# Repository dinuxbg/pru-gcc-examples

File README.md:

# Example projects for the GNU PRU toolchain

The pru-gcc toolchain source and build instructions are located at https://github.com/dinuxbg/gnupru .

The following simple examples are available. Check the README.md in each subdirectory for detailed instructions.

## blinking-led
The "hello world" example of the embedded world. Both PRU cores of a Beaglebone Black are started to toggle GPIOs. PRU0 core is programmed in C, while the firmware for PRU1 core is written in assembler.

Two host loader examples are provided - one for the old UIO mechanism, and one for the new Remoteproc driver.

## blinking-led++
Blinking led firmware written in C++.

## button-blinking-led
Button-controlled blinking LED. Shows both basic input and basic output.

## hc-sr04-range-sensor
Remoteproc/rpmsg example for measuring distance using the HC-SR04 ultrasound range sensor.

## md5-check
Calculate MD5 checksum for a known data chunk on both the ARM loader and one PRU core. Then UIO-based loader reads and compares the two checksums.

## ov7670-cam
PRUs on a Beaglebone White fetch RGB565 streams from two OV7670 camera modules. The UIO host-side loader then saves the images from the shared DDR-SDRAM memory into PPM files. The example shows how to access shared buffers in DDR-SDRAM, and how to write time-critical code sequences in inline assembly.

## sim-hello
Simulate your PRU executable on your PC. Note that pru-run is an ISA only simulator. Digital I/O is not simulated. Neither is OCP access.

## sim-hello++
Same simulator project as sim-hello, but written in C++ instead of C.

## External Projects
Some examples are too complex to pile up in this repository, yet could be useful as a reference.
  * [BeagleMic Microphone Array](https://gitlab.com/dinuxbg/beaglemic)

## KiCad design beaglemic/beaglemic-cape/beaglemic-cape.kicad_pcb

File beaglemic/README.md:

# BeagleMic 16-channel PDM Audio Capture

# Introduction
Ever wanted to record audio from 16 PDM microphones simultanously? Now you can with a BeagleMic running on a [PocketBeagle](https://beagleboard.org/pocket) or [BeagleBone AI](https://bbb.io/ai)

Yes, you could opt for the much simpler I2S microphones. But then you won't have fun writing assembly to capture and process sixteen digital signals at more than 2MHz sample rate.

Current firmware supports:

| Feature                    | Support           |
|----------------------------|-------------------|
| PDM Bit Clock              | 2,273 MHz         |
| PCM Output Bits Per Sample | 16 bps            |
| PCM Output Sample Rate     | 35511 Samples/sec |

# Hardware
The schematic is simple. PDM microphones' digital outputs are connected directly to the PRU input pins. The PRU also drives the bit clock. I have tested on PocketBeagle and BeagleBone AI.

| PocketBeagle | BBAI  | PRU Pin | Type  | Signal               |
|----------------------|---------|-------|----------------------|
| P2.24        | P9.11 | R30_14  | Output| PDM Bit Clock        |
| P1.36        | P8.44 | R31_0   | Input | MIC0 and MIC1 Data   |
| P1.33        | P8.41 | R31_1   | Input | MIC2 and MIC3 Data   |
| P2.32        | P8.42 | R31_2   | Input | MIC4 and MIC5 Data   |
| P2.30        | P8.39 | R31_3   | Input | MIC6 and MIC7 Data   |
| P1.31        | P8.40 | R31_4   | Input | MIC8 and MIC9 Data   |
| P2.34        | P8.37 | R31_5   | Input | MIC10 and MIC11 Data |
| P2.28        | P8.38 | R31_6   | Input | MIC12 and MIC13 Data |
| P1.29        | P8.36 | R31_7   | Input | MIC14 and MIC15 Data |

Optionally, high-level software may visualize detected audio direction using a stripe of 16 LEDs hooked to two 74HC595 shift registers:

| PocketBeagle | PB GPIO | BBAI  | BBAI GPIO | Signal |
|--------------|---------|-------|-----------|--------|
|              |         | P9.30 | gpio5_12  | DS     |
|              |         | P9.28 | gpio4_17  | SHCP   |
|              |         | P9.23 | gpio7_11  | STCP   |

For each microphone pair, one microphone is configured to output data on the rising clock edge, and the other is configured to output data on the falling edge. This way we need only 8 input GPIOs to capture data from all 16 microphones.

Microphone breakout board and a PocketBeagle Cape are provided in KiCad format.

Unfortunately the breakout board is essential for a home DIY user like me, since all PDM microphones I could find are BGA. There are numerous youtube guides how to solder BGAs at home using a skillet or a toaster oven.

# Software
PRU0 takes care of driving the PDM bit clock and capturing the microphone bit data. It then runs a CIC filter to convert PDM to PCM, and feeds PCM data to PRU1.

PRU1 is retransmitting PCM data from PRU0 down to the ARM host. RPMSG is used for control commands. Shared DDRAM buffers are used for audio data.

Host audio driver presents a standard ALSA audio card, so that arecord and other standard tools can be readily used.

# Running The Example on PocketBeagle

    # Build kernel module
    sudo apt update
    sudo apt install build-essential linux-headers-`uname -r`
    cd driver
    make
    # Install kernel module
    sudo cp beaglemic.ko /lib/modules/`uname -r`/kernel/drivers/rpmsg/
    sudo depmod -a

    # Load the driver
    sudo modprobe beaglemic

    # Build PRU firmware
    cd pru
    make
    # Start the new PRU firmware
    sudo ./start.sh

    # Record audio
    arecord  -r32000  -c16 -f S16_LE -t wav out.wav
    # Hit Ctrl+C to stop.

# Running The Example on BeagleBone AI

    # Prebuilt BB AI is provided in this repo. For corresponding
    # source change, see driver/0001-Initial-BeagleMic-DTS-for-BBAI.patch
    sudo cp driver/am5729-beagleboneai-beaglemic.dtb /boot/dtbs/`uname -r`/
    sudo sed -i -e 's@#dtb=@dtb=am5729-beagleboneai-beaglemic.dtb@g' /boot/uEnv.txt
    sync
    sudo reboot

    # Build kernel module
    sudo apt update
    sudo apt install build-essential linux-headers-`uname -r`
    cd driver
    make
    # Install kernel module
    sudo cp beaglemic.ko /lib/modules/`uname -r`/kernel/drivers/rpmsg/
    sudo depmod -a

    # Load the driver
    sudo modprobe beaglemic

    # Build PRU firmware
    cd pru
    make
    # Start the new PRU firmware
    sudo ./start-bbai.sh

    # Record audio. Use second audio card, since first one is
    # the onboard HDMI.
    arecord  -D hw:1,0 -r32000  -c16 -f S16_LE -t wav out.wav
    # Hit Ctrl+C to stop.

# Folder Structure

 * beaglemic-cape - Universal cape for BeagleBone AI, PocketBeagle and iCE40HX8K-EVB. Work in progress.
 * driver - Host ALSA audio driver.
 * inmp621-breakout - INMP621 Microphone breakout. Designed to be used with beaglemic-cape. Work in progress.
 * libs - Library code. Currently contains code to drive LED ring for beaglemic-cape.
 * pocket-cape - PocketBeagle cape to be used with spm0423hd4h-breakout.
 * pru - PRU firmware.
 * spm0423hd4h-breakout - SPM0432HD4H microphone breakout. Designed to be used with pocket-cape.

# Further Work
A few ideas to improve the design:

 * If input is limited to 8 microphones, then process and output 24bit PCM data.
 * Move comb filters to PRU1, and try to add more integrators in PRU0.
 * Clean-up the cape PCB.
   * If possible, leave headers for Class-D output from spare PRUs.

# References
 * [CIC Filter Introduction](https://dspguru.com/dsp/tutorials/cic-filter-introduction/)
 * [Another CIC Filter Article](http://www.tsdconseil.fr/log/scriptscilab/cic/cic-en.pdf)
 * [Series of PDM articles and software implementations](https://curiouser.cheshireeng.com/category/projects/pdm-microphone-toys/)
 * [Another CIC Filter Article](https://www.embedded.com/design/configurable-systems/4006446/Understanding-cascaded-integrator-comb-filters)
 * [Datasheet for the PDM microphones I've used](http://media.digikey.com/PDF/Data Sheets/Knowles Acoustics PDFs/SPM0423HD4H-WB.pdf)
 * [Inspiration for high-bandwidth data acquisition](https://github.com/ZeekHuge/BeagleScope)

# Other Resources
 * https://github.com/introlab/16SoundsUSB
 * https://github.com/introlab/odas
 * https://respeaker.io/make_a_smart_speaker/

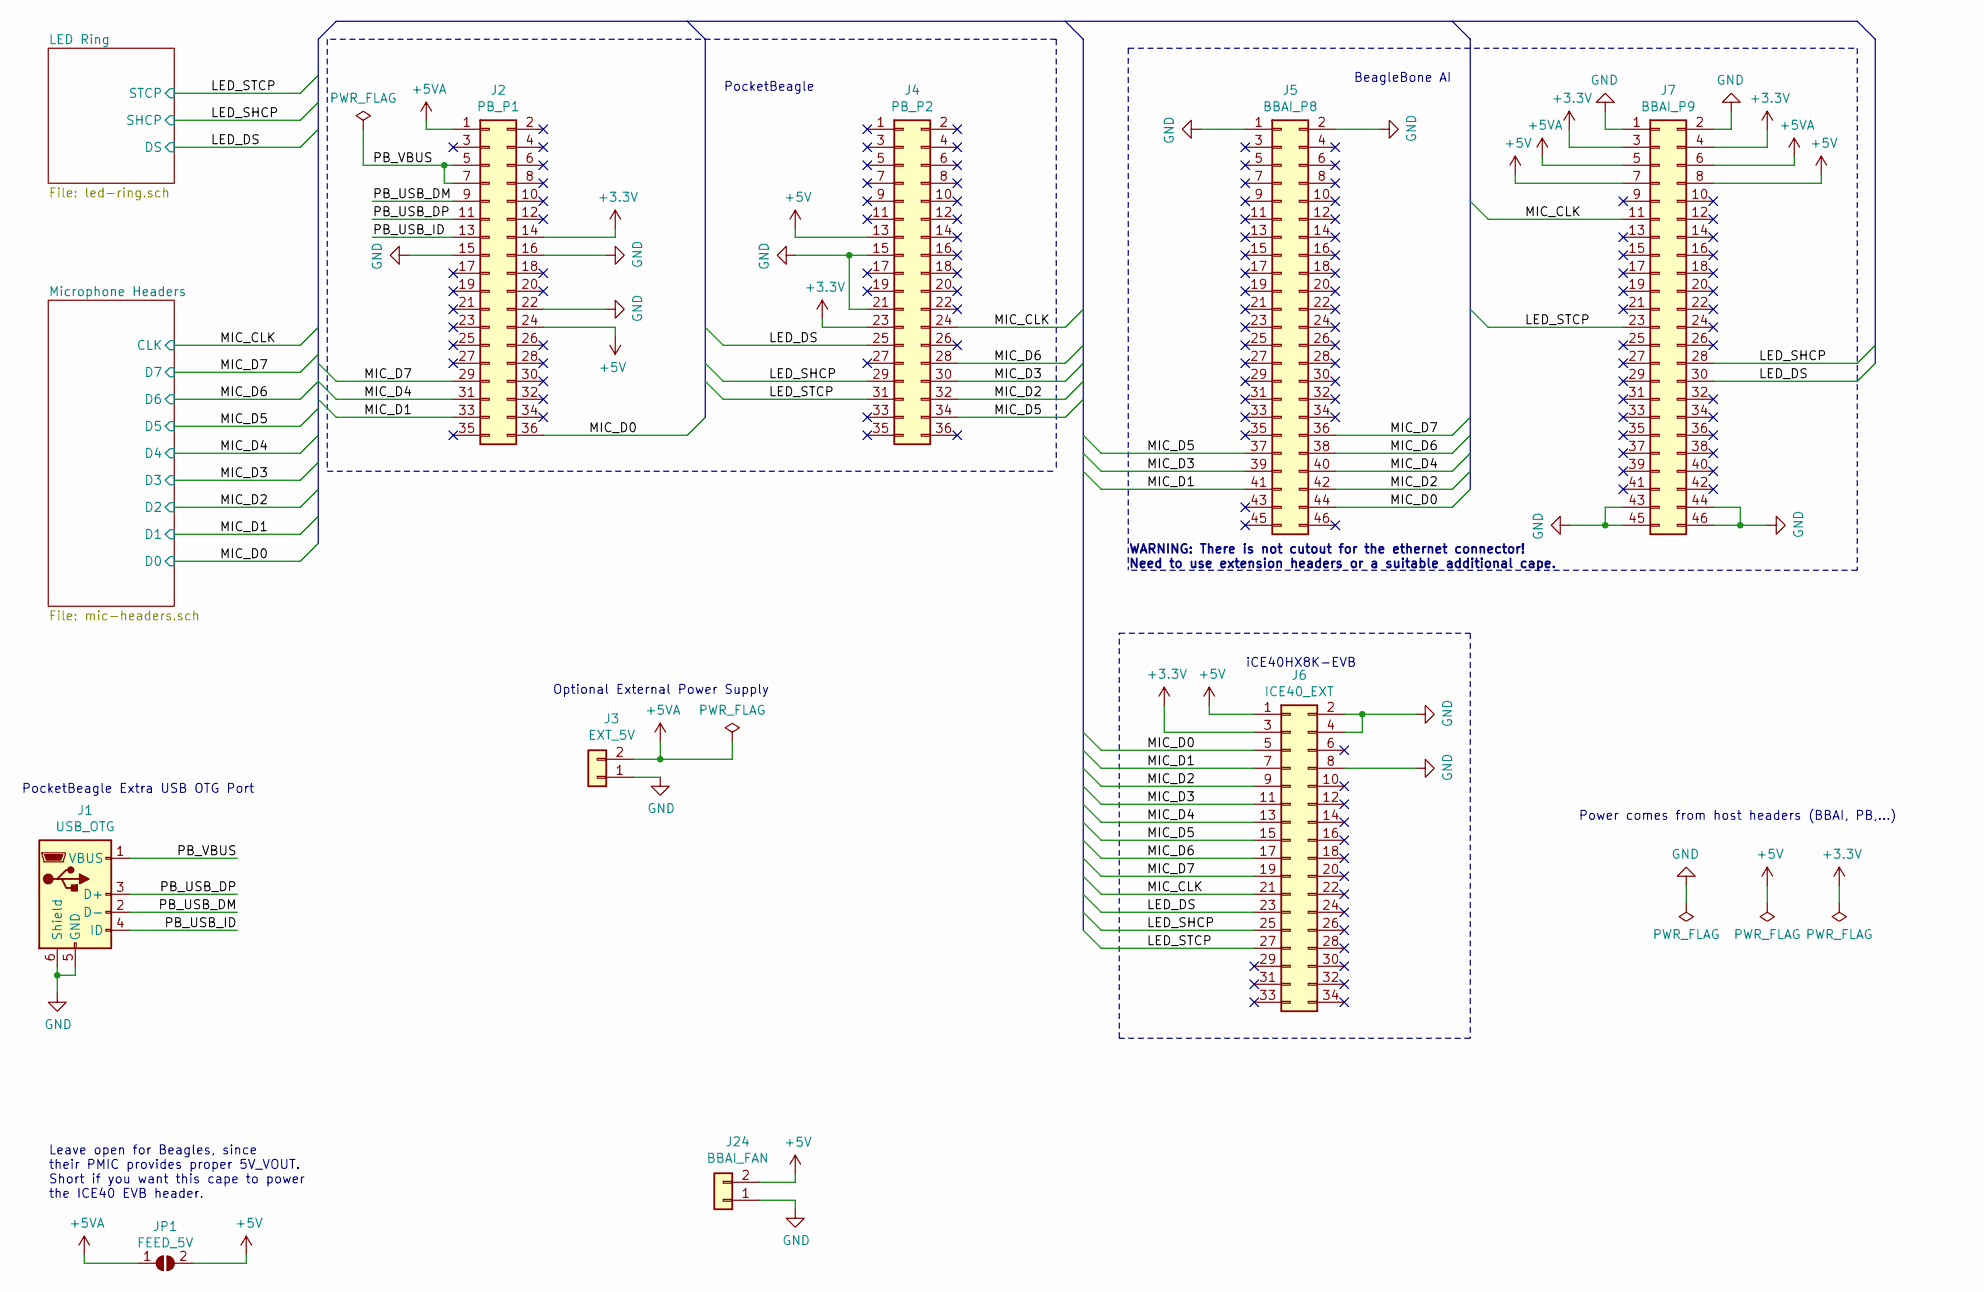
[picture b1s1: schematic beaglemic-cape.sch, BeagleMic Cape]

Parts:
J1: USB_OTG; USB_Micro-B_Tensility_54-00023_Vertical_CircularHoles
J2: PB_P1; PinHeader_2x18_P2.54mm_Vertical
J3: EXT_5V; PinHeader_1x02_P2.54mm_Vertical
J4: PB_P2; PinHeader_2x18_P2.54mm_Vertical
J5: BBAI_P8; PinSocket_2x23_P2.54mm_Vertical
J6: ICE40_EXT; PinSocket_2x17_P2.54mm_Vertical
J7: BBAI_P9; PinSocket_2x23_P2.54mm_Vertical
J24: BBAI_FAN; PinHeader_1x02_P2.54mm_Vertical
JP1: FEED_5V; SolderJumper-2_P1.3mm_Open_RoundedPad1.0x1.5mm

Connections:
+3V3: J2.14, J4.23, J6.3, J7.3, J7.4; also elsewhere on the board
+5V: J2.24, J4.13, J6.1, J7.7, J7.8, J24.2, JP1.2 (B); also elsewhere on the board
+5VA: J2.1, J3.2, J7.5, J7.6, JP1.1 (A)
/LED_DS: J4.25, J6.23, J7.30; also elsewhere on the board
/LED_SHCP: J4.29, J6.25, J7.28; also elsewhere on the board
/LED_STCP: J4.31, J6.27, J7.23; also elsewhere on the board
/MIC_CLK: J4.24, J6.21, J7.11; also elsewhere on the board
/MIC_D0: J2.36, J5.44, J6.5; also elsewhere on the board
/MIC_D1: J2.33, J5.41, J6.7; also elsewhere on the board
/MIC_D2: J4.32, J5.42, J6.9; also elsewhere on the board
/MIC_D3: J4.30, J5.39, J6.11; also elsewhere on the board
/MIC_D4: J2.31, J5.40, J6.13; also elsewhere on the board
/MIC_D5: J4.34, J5.37, J6.15; also elsewhere on the board
/MIC_D6: J4.28, J5.38, J6.17; also elsewhere on the board
/MIC_D7: J2.29, J5.36, J6.19; also elsewhere on the board
/PB_USB_DM: J1.2 (D-), J2.9
/PB_USB_DP: J1.3 (D+), J2.11
/PB_USB_ID: J1.4 (ID), J2.13
/PB_VBUS: J1.1 (VBUS), J2.5, J2.7
GND: J1.5 (GND), J1.6 (Shield), J2.15, J2.16, J2.22, J3.1, J4.15, J4.21, J5.1, J5.2, J6.2, J6.4, J6.8, J7.1, J7.2, J7.43, J7.44, J7.45, J7.46, J24.1; also elsewhere on the board

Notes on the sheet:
Power comes from host headers (BBAI, PB,...)
PocketBeagle Extra USB OTG Port
Optional External Power Supply
Leave open for Beagles, since their PMIC provides proper 5V_VOUT. Short if you want this cape to power the ICE40 EVB header.
iCE40HX8K-EVB
PocketBeagle
BeagleBone AI
WARNING: There is not cutout for the ethernet connector! Need to use extension headers or a suitable additional cape.

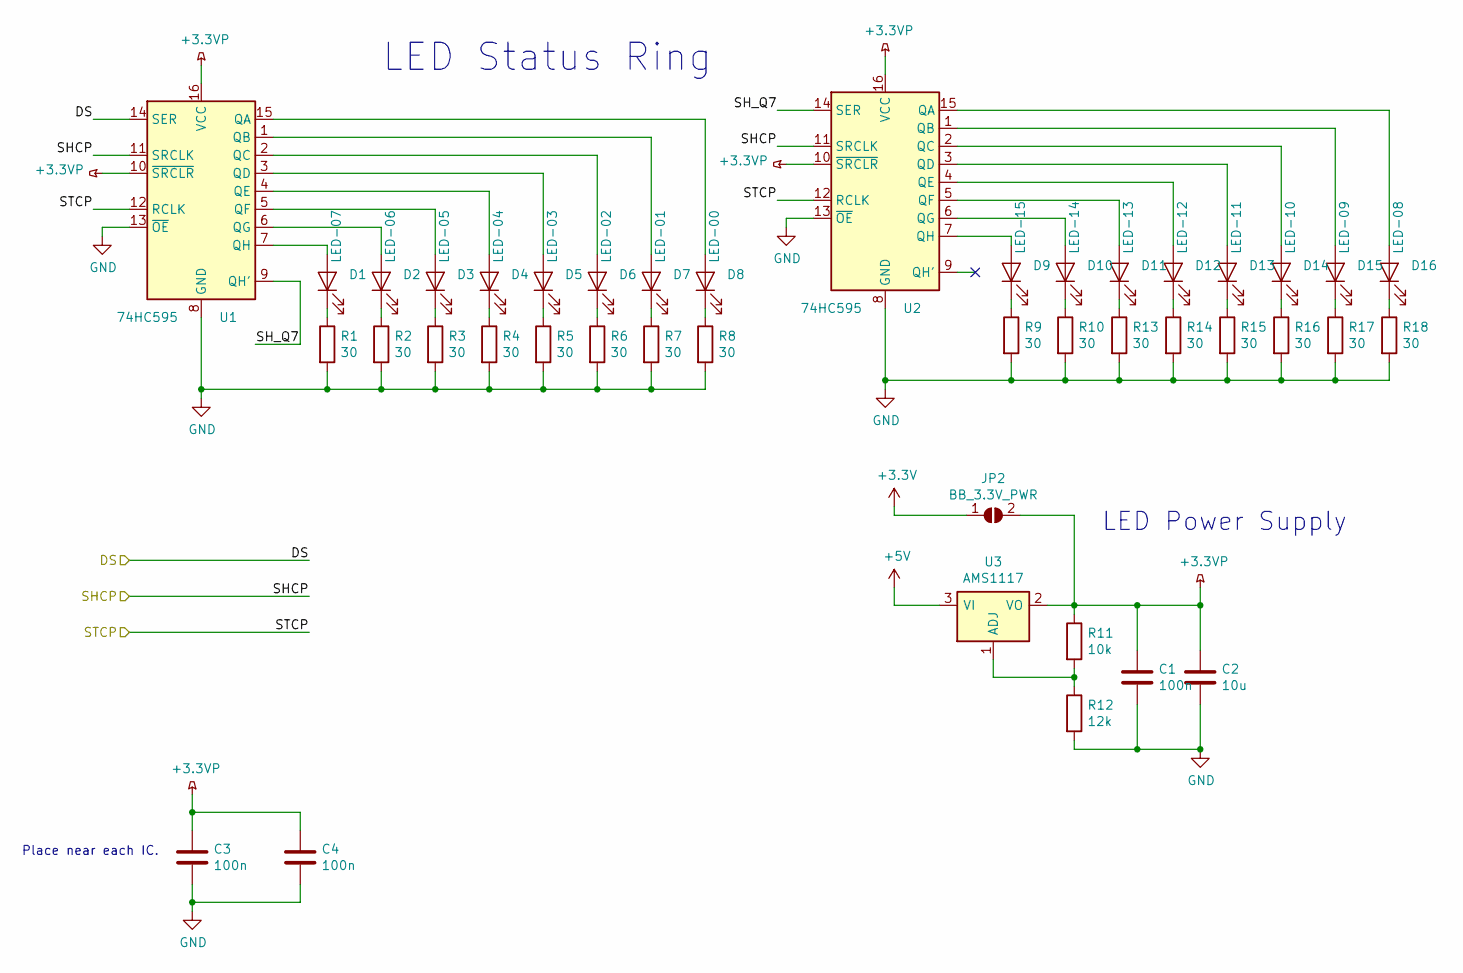
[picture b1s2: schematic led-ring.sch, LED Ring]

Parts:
C1, C3, C4: 100n; C_0805_2012Metric
C2: 10u; C_0805_2012Metric
D1: LED-07; LED_0805_2012Metric
D2: LED-06; LED_0805_2012Metric
D3: LED-05; LED_0805_2012Metric
D4: LED-04; LED_0805_2012Metric
D5: LED-03; LED_0805_2012Metric
D6: LED-02; LED_0805_2012Metric
D7: LED-01; LED_0805_2012Metric
D8: LED-00; LED_0805_2012Metric
D9: LED-15; LED_0805_2012Metric
D10: LED-14; LED_0805_2012Metric
D11: LED-13; LED_0805_2012Metric
D12: LED-12; LED_0805_2012Metric
D13: LED-11; LED_0805_2012Metric
D14: LED-10; LED_0805_2012Metric
D15: LED-09; LED_0805_2012Metric
D16: LED-08; LED_0805_2012Metric
JP2: BB_3.3V_PWR; SolderJumper-2_P1.3mm_Open_RoundedPad1.0x1.5mm
R1, R2, R3, R4, R5, R6, R7, R8, R9, R10, R13, R14, R15, R16, R17, R18: 30; R_0805_2012Metric
R11: 10k; R_0805_2012Metric
R12: 12k; R_0805_2012Metric
U1, U2: 74HC595; TSSOP-16_4.4x5mm_P0.65mm
U3: AMS1117; SOT-223-3_TabPin2

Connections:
+3.3VP: C1.1, C2.1, C3.1, C4.1, JP2.2 (B), R11.1, U1.10 (~SRCLR), U1.16 (VCC), U2.10 (~SRCLR), U2.16 (VCC), U3.2 (VO)
+3V3: JP2.1 (A); also elsewhere on the board
+5V: U3.3 (VI); also elsewhere on the board
/LED Ring/SH_Q7: U1.9 (QH'), U2.14 (SER)
/LED_DS: U1.14 (SER); also elsewhere on the board
/LED_SHCP: U1.11 (SRCLK), U2.11 (SRCLK); also elsewhere on the board
/LED_STCP: U1.12 (RCLK), U2.12 (RCLK); also elsewhere on the board
GND: C1.2, C2.2, C3.2, C4.2, R1.2, R2.2, R3.2, R4.2, R5.2, R6.2, R7.2, R8.2, R9.2, R10.2, R12.2, R13.2, R14.2, R15.2, R16.2, R17.2, R18.2, U1.8 (GND), U1.13 (~OE), U2.8 (GND), U2.13 (~OE); also elsewhere on the board
unnamed: D1.1 (K), R1.1
unnamed: D1.2 (A), U1.7 (QH)
unnamed: D2.1 (K), R2.1
unnamed: D2.2 (A), U1.6 (QG)
unnamed: D3.1 (K), R3.1
unnamed: D3.2 (A), U1.5 (QF)
unnamed: D4.1 (K), R4.1
unnamed: D4.2 (A), U1.4 (QE)
unnamed: D5.1 (K), R5.1
unnamed: D5.2 (A), U1.3 (QD)
unnamed: D6.1 (K), R6.1
unnamed: D6.2 (A), U1.2 (QC)
unnamed: D7.1 (K), R7.1
unnamed: D7.2 (A), U1.1 (QB)
unnamed: D8.1 (K), R8.1
unnamed: D8.2 (A), U1.15 (QA)
unnamed: D9.1 (K), R9.1
unnamed: D9.2 (A), U2.7 (QH)
unnamed: D10.1 (K), R10.1
unnamed: D10.2 (A), U2.6 (QG)
unnamed: D11.1 (K), R13.1
unnamed: D11.2 (A), U2.5 (QF)
unnamed: D12.1 (K), R14.1
unnamed: D12.2 (A), U2.4 (QE)
unnamed: D13.1 (K), R15.1
unnamed: D13.2 (A), U2.3 (QD)
unnamed: D14.1 (K), R16.1
unnamed: D14.2 (A), U2.2 (QC)
unnamed: D15.1 (K), R17.1
unnamed: D15.2 (A), U2.1 (QB)
unnamed: D16.1 (K), R18.1
unnamed: D16.2 (A), U2.15 (QA)
unnamed: R11.2, R12.1, U3.1 (ADJ)

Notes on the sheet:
LED Status Ring
LED Power Supply
Place near each IC.

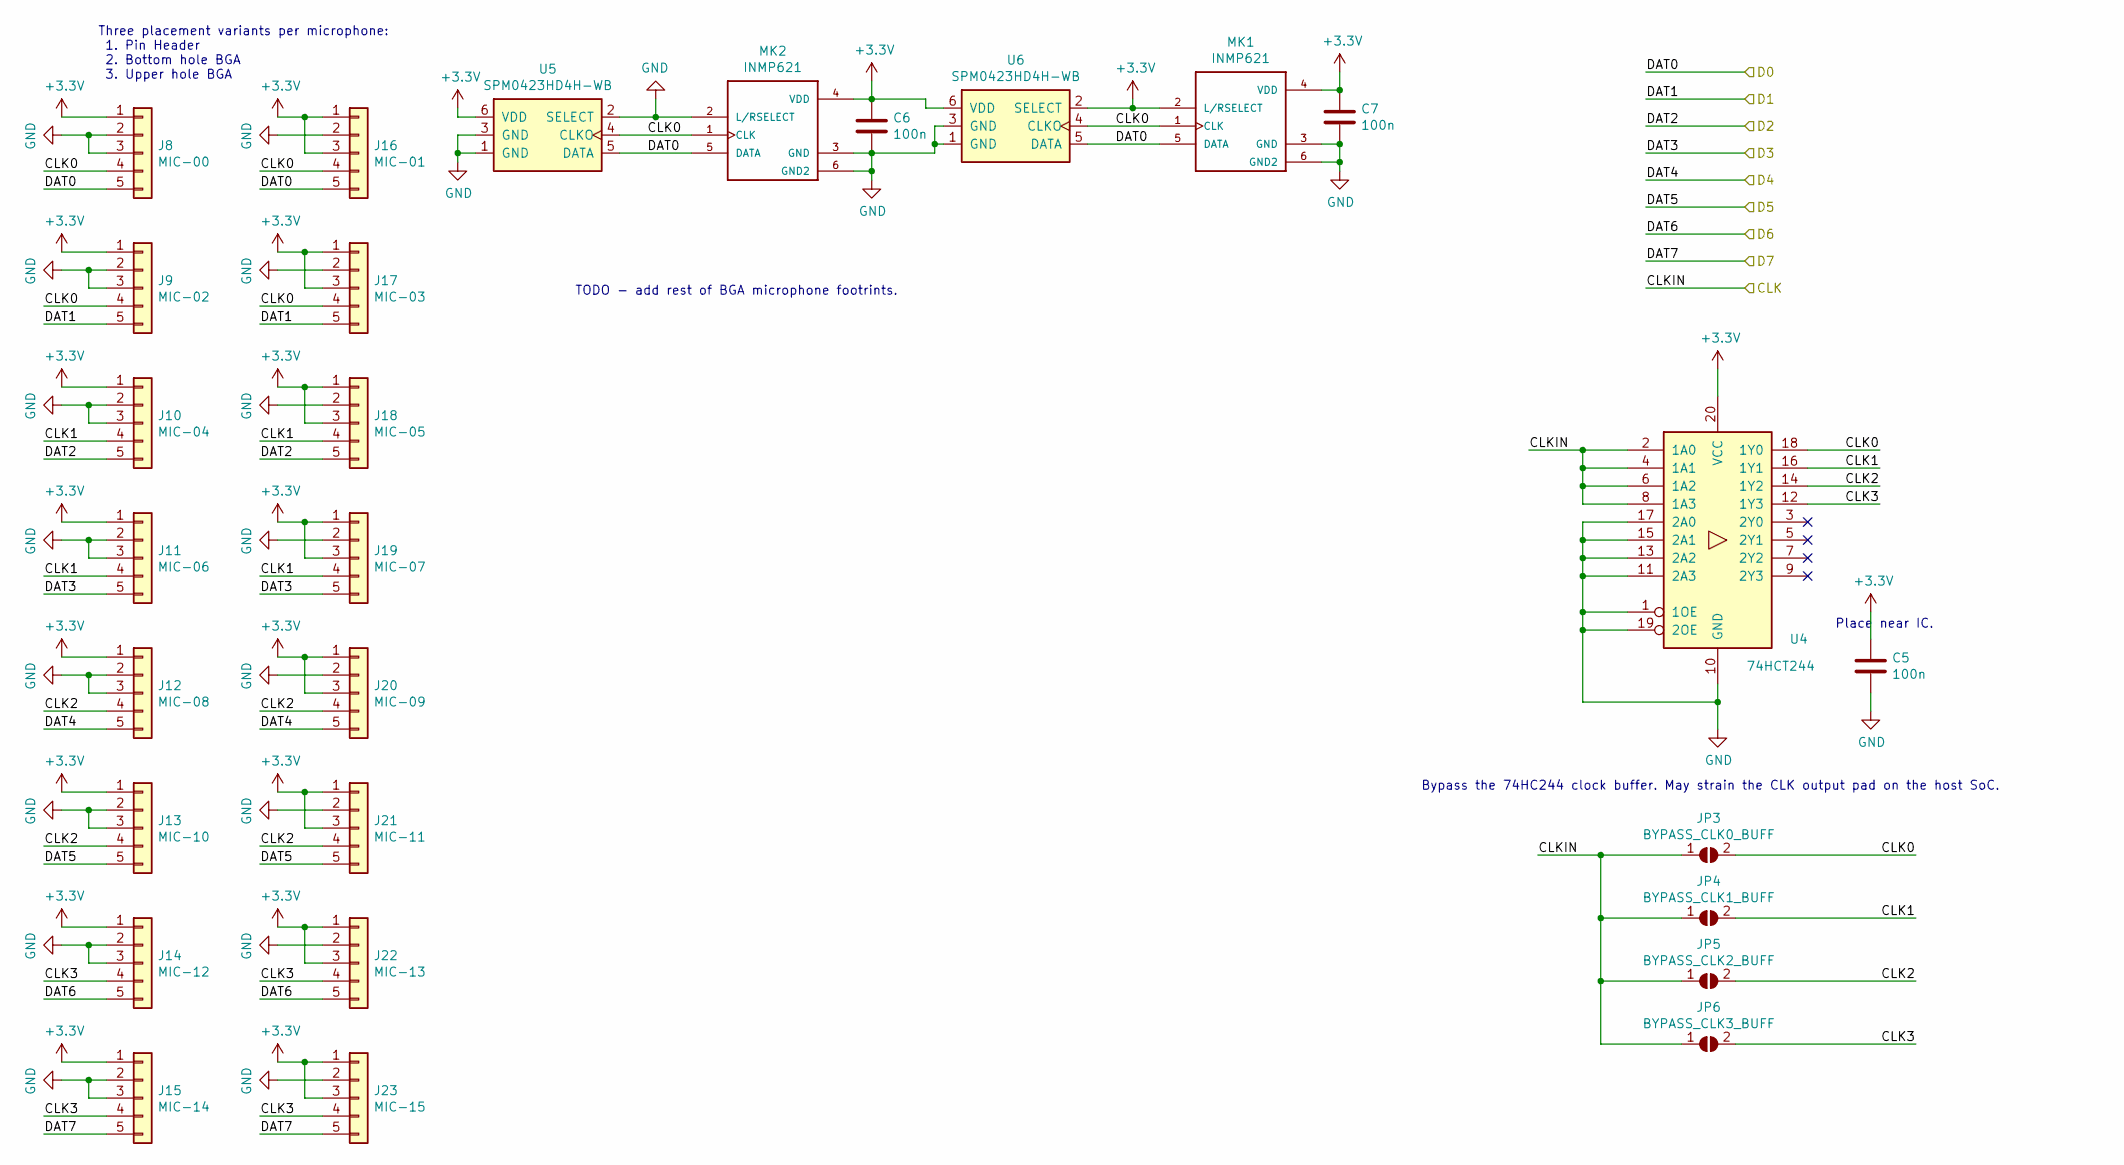
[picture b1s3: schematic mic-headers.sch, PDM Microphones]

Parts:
C5, C6, C7: 100n; C_0805_2012Metric
J8: MIC-00; PinSocket_1x05_P2.54mm_Horizontal
J9: MIC-02; PinSocket_1x05_P2.54mm_Horizontal
J10: MIC-04; PinSocket_1x05_P2.54mm_Horizontal
J11: MIC-06; PinSocket_1x05_P2.54mm_Horizontal
J12: MIC-08; PinSocket_1x05_P2.54mm_Horizontal
J13: MIC-10; PinSocket_1x05_P2.54mm_Horizontal
J14: MIC-12; PinSocket_1x05_P2.54mm_Horizontal
J15: MIC-14; PinSocket_1x05_P2.54mm_Horizontal
J16: MIC-01; PinSocket_1x05_P2.54mm_Horizontal
J17: MIC-03; PinSocket_1x05_P2.54mm_Horizontal
J18: MIC-05; PinSocket_1x05_P2.54mm_Horizontal
J19: MIC-07; PinSocket_1x05_P2.54mm_Horizontal
J20: MIC-09; PinSocket_1x05_P2.54mm_Horizontal
J21: MIC-11; PinSocket_1x05_P2.54mm_Horizontal
J22: MIC-13; PinSocket_1x05_P2.54mm_Horizontal
J23: MIC-15; PinSocket_1x05_P2.54mm_Horizontal
JP3: BYPASS_CLK0_BUFF; SolderJumper-2_P1.3mm_Open_RoundedPad1.0x1.5mm
JP4: BYPASS_CLK1_BUFF; SolderJumper-2_P1.3mm_Open_RoundedPad1.0x1.5mm
JP5: BYPASS_CLK2_BUFF; SolderJumper-2_P1.3mm_Open_RoundedPad1.0x1.5mm
JP6: BYPASS_CLK3_BUFF; SolderJumper-2_P1.3mm_Open_RoundedPad1.0x1.5mm
MK1, MK2: INMP621; MK_INMP621
U4: 74HCT244; TSSOP-20_4.4x6.5mm_P0.65mm
U5, U6: SPM0423HD4H-WB; BGA_6

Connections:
+3V3: C5.1, C6.1, C7.1, J8.1, J9.1, J10.1, J11.1, J12.1, J13.1, J14.1, J15.1, J16.1, J16.3, J17.1, J17.3, J18.1, J18.3, J19.1, J19.3, J20.1, J20.3, J21.1, J21.3, J22.1, J22.3, J23.1, J23.3, MK1.2 (L/RSELECT), MK1.4 (VDD), MK2.4 (VDD), U4.20 (VCC), U5.6 (VDD), U6.2 (SELECT), U6.6 (VDD); also elsewhere on the board
/MIC_CLK: JP3.1 (A), JP4.1 (A), JP5.1 (A), JP6.1 (A), U4.2 (1A0), U4.4 (1A1), U4.6 (1A2), U4.8 (1A3); also elsewhere on the board
/MIC_D0: J8.5, J16.5, MK1.5 (DATA), MK2.5 (DATA), U5.5 (DATA), U6.5 (DATA); also elsewhere on the board
/MIC_D1: J9.5, J17.5; also elsewhere on the board
/MIC_D2: J10.5, J18.5; also elsewhere on the board
/MIC_D3: J11.5, J19.5; also elsewhere on the board
/MIC_D4: J12.5, J20.5; also elsewhere on the board
/MIC_D5: J13.5, J21.5; also elsewhere on the board
/MIC_D6: J14.5, J22.5; also elsewhere on the board
/MIC_D7: J15.5, J23.5; also elsewhere on the board
/Microphone Headers/CLK0: J8.4, J9.4, J16.4, J17.4, JP3.2 (B), MK1.1 (CLK), MK2.1 (CLK), U4.18 (1Y0), U5.4 (CLKO), U6.4 (CLKO)
/Microphone Headers/CLK1: J10.4, J11.4, J18.4, J19.4, JP4.2 (B), U4.16 (1Y1)
/Microphone Headers/CLK2: J12.4, J13.4, J20.4, J21.4, JP5.2 (B), U4.14 (1Y2)
/Microphone Headers/CLK3: J14.4, J15.4, J22.4, J23.4, JP6.2 (B), U4.12 (1Y3)
GND: C5.2, C6.2, C7.2, J8.2, J8.3, J9.2, J9.3, J10.2, J10.3, J11.2, J11.3, J12.2, J12.3, J13.2, J13.3, J14.2, J14.3, J15.2, J15.3, J16.2, J17.2, J18.2, J19.2, J20.2, J21.2, J22.2, J23.2, MK1.3 (GND), MK1.6 (GND2), MK2.2 (L/RSELECT), MK2.3 (GND), MK2.6 (GND2), U4.1 (1OE), U4.10 (GND), U4.11 (2A3), U4.13 (2A2), U4.15 (2A1), U4.17 (2A0), U4.19 (2OE), U5.1 (GND), U5.2 (SELECT), U5.3 (GND), U6.1 (GND), U6.3 (GND); also elsewhere on the board

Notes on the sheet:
Bypass the 74HC244 clock buffer. May strain the CLK output pad on the host SoC.
Place near IC.
Three placement variants per microphone: 1. Pin Header 2. Bottom hole BGA 3. Upper hole BGA
TODO - add rest of BGA microphone footrints.

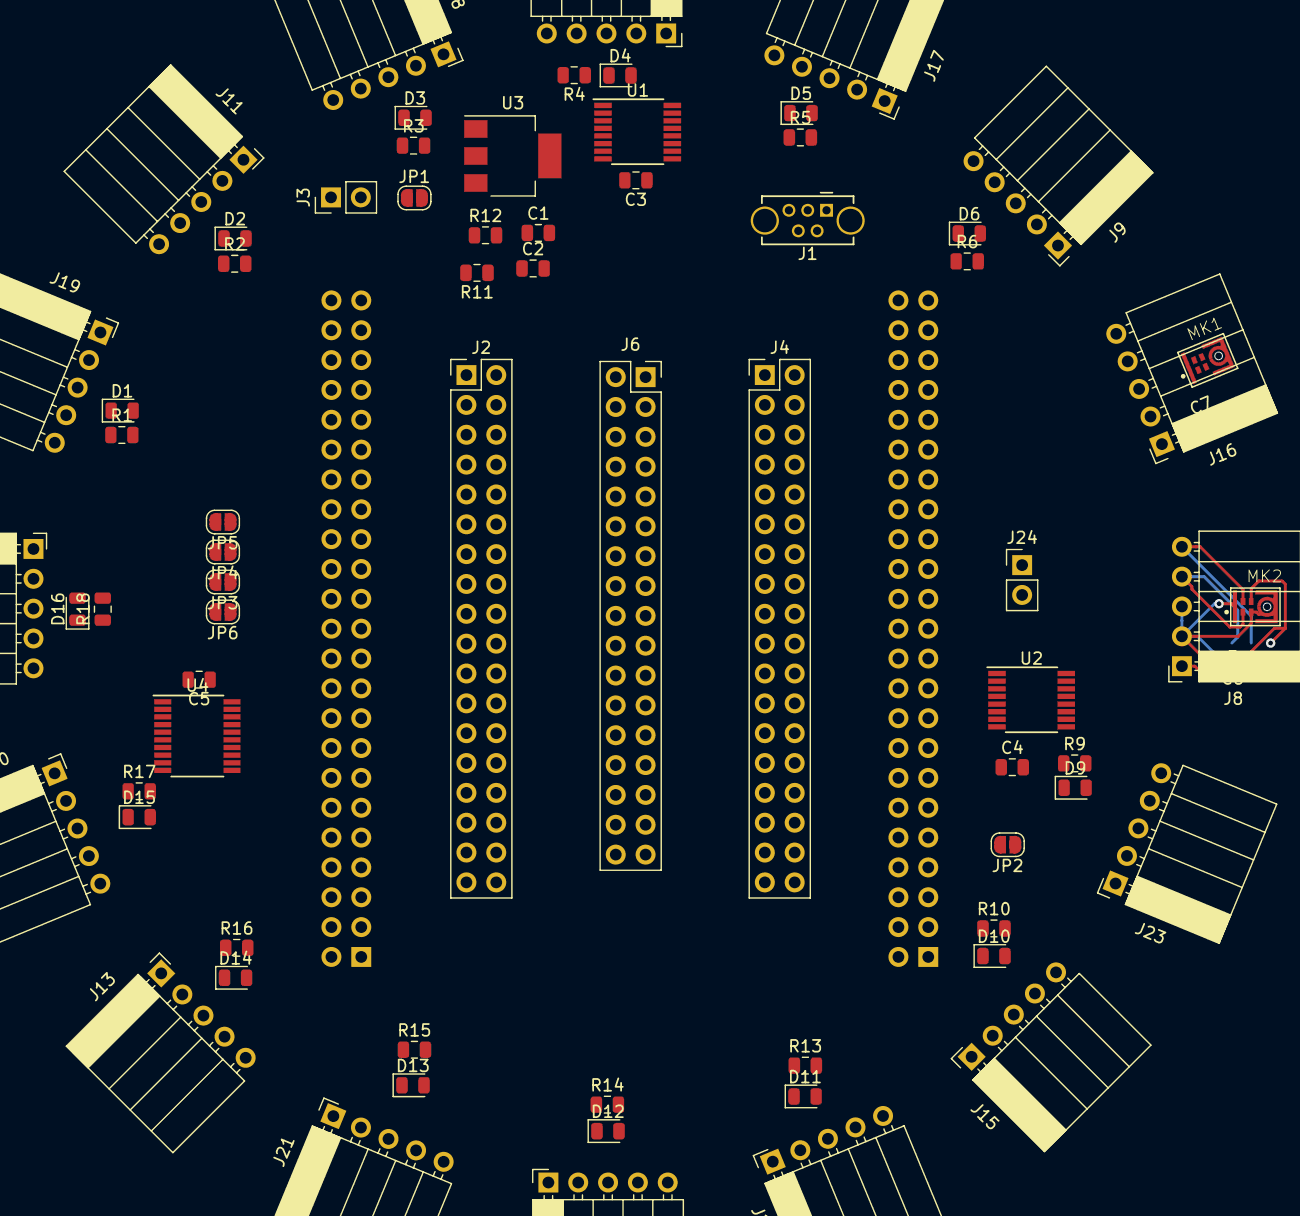
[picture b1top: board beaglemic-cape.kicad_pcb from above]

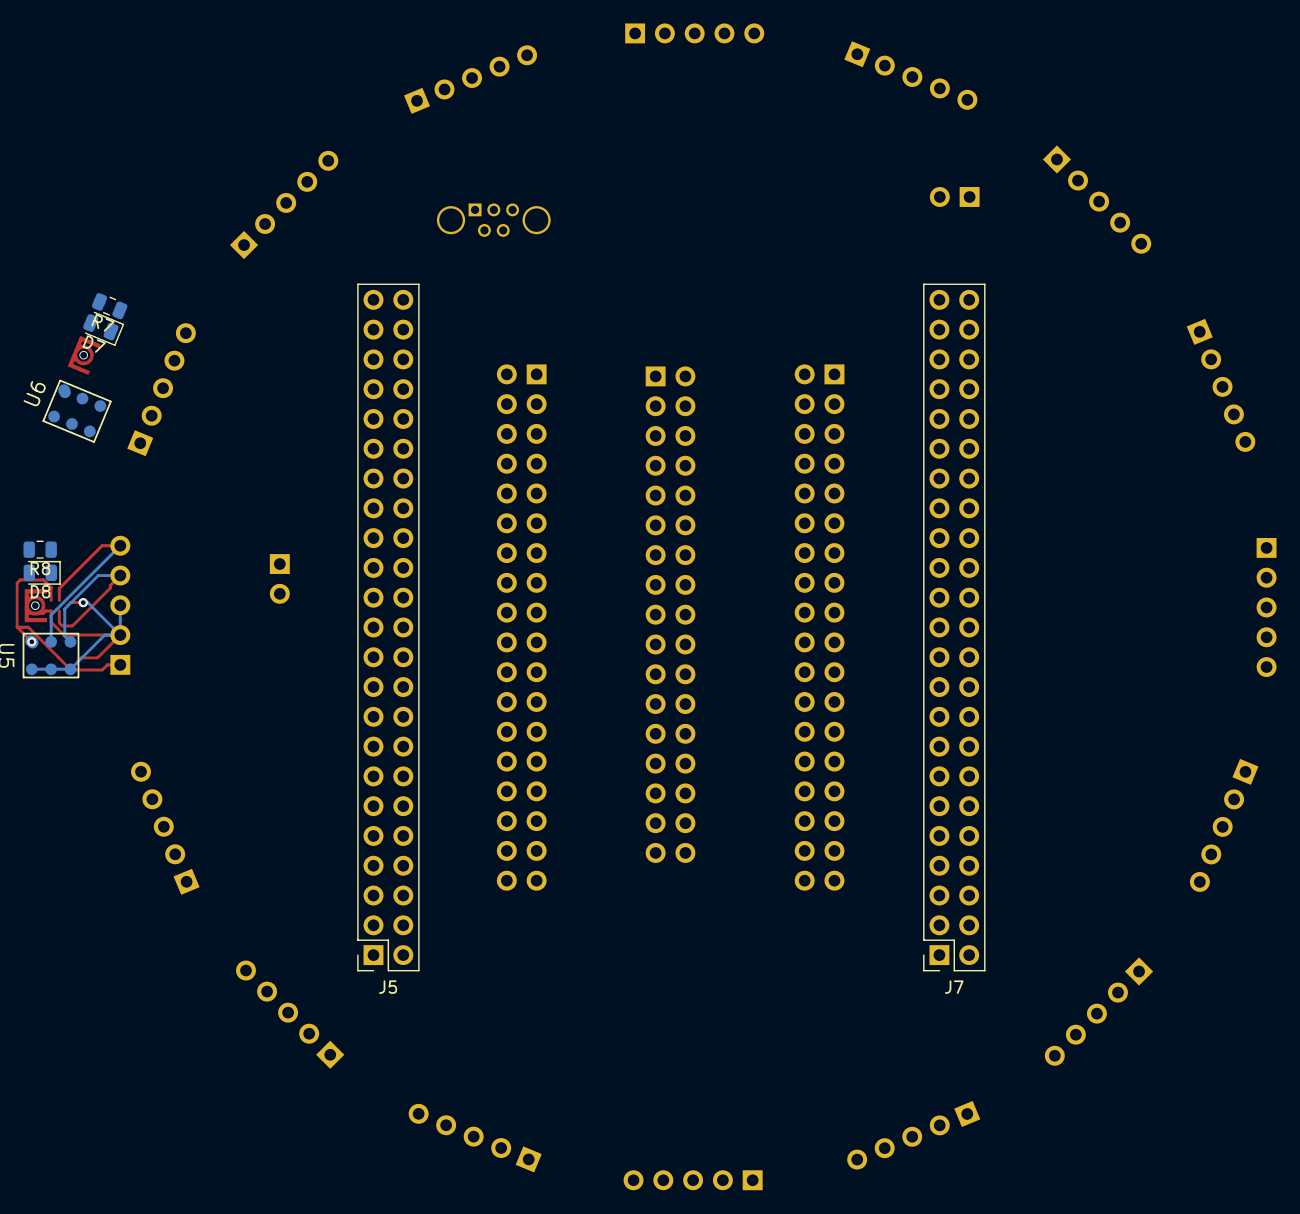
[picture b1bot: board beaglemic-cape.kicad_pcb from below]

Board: 2 copper layers, 79 parts (8 on the bottom side), 59 nets.

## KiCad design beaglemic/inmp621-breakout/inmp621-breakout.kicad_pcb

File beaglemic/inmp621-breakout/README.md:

This is a KiCAD project for a simple breakout board for the INMP621 PDM mems microphone.

This board deliberately does not follow the spm0423hd4h-breakout pinout. The spm0423hd4h-breakout was designed to be connected via long wires to a main board, so it had:
 * Two microphones per breakout board, to reduce overall wiring.
 * GND wire between all other signals, to reduce inter-signal EMI when using long flat cables.

Soldering flat cables proved too cumbersome, so I abandoned that design. While soft cable wiring is still possible, the new INMP621 breakout board is envisioned to be directly connected to a main board using pin headers.. For compatibility's sake, I used same pinout as [Adafruit's PDM board](https://www.adafruit.com/product/3492).

References:
 * Microphone footprint, 3D model and schematics symbol are taken from https://www.snapeda.com/parts/INMP621/InvenSense/view-part/?ref=digikey . Footprint has minor modification to "break" the ground track and ease the data wires routing.

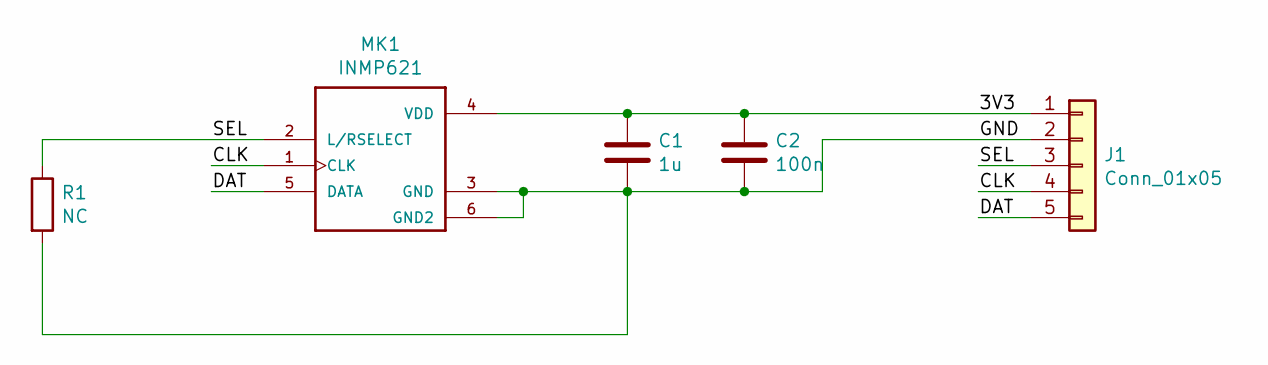
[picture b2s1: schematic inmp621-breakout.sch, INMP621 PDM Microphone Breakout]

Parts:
C1: 1u; C_0805_2012Metric
C2: 100n; C_0805_2012Metric
J1: Conn_01x05; PinHeader_1x05_P2.54mm_Vertical
MK1: INMP621; MK_INMP621
R1: NC; R_0805_2012Metric

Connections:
/3V3: C1.1, C2.1, J1.1, MK1.4 (VDD)
/CLK: J1.4, MK1.1 (CLK)
/DAT: J1.5, MK1.5 (DATA)
/GND: C1.2, C2.2, J1.2, MK1.3 (GND), MK1.6 (GND2), R1.2
/SEL: J1.3, MK1.2 (L/RSELECT), R1.1

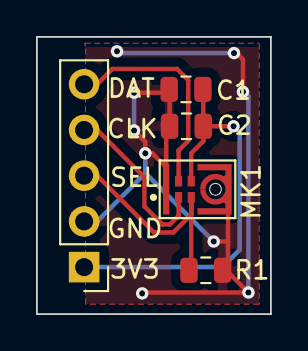
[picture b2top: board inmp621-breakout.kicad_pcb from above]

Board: 2 copper layers, 13.0 x 15.4 mm, 5 parts (0 on the bottom side), 5 nets.

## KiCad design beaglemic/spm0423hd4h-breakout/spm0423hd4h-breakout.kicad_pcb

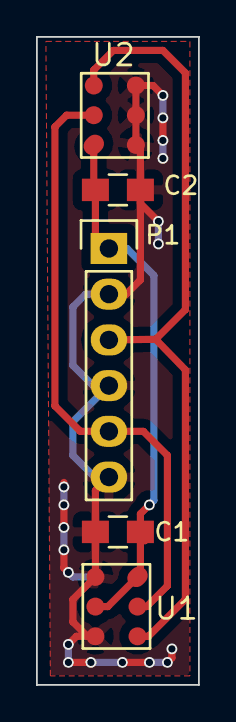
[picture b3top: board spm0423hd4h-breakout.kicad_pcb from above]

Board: 2 copper layers, 9.0 x 36.0 mm, 5 parts (0 on the bottom side), 4 nets.

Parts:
C1, C2: 100n; C_0805_HandSoldering
P1: CONN_01X06; Pin_Header_Straight_1x06
U1: MIC1; BGA_6
U2: MIC0; BGA_6

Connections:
/CLK: P1.3, U1.4, U2.4
/D: P1.5, U1.5, U2.5
GND: C1.2, C2.2, P1.2, P1.4, P1.6, U1.1, U1.3, U2.1, U2.2, U2.3
VDD: C1.1, C2.1, P1.1, U1.2, U1.6, U2.6

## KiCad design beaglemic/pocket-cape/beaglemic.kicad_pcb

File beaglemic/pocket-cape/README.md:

# Errata
 1. Standard USB A connector does not fit properly. With some pin bending and care it can be mounted, though.
 2. VI and VB pins must be shorted (P1 pins 5 and 7).

# References
This PocketBeagle Cape is heavily based on https://github.com/beagleboard/pocketbeagle

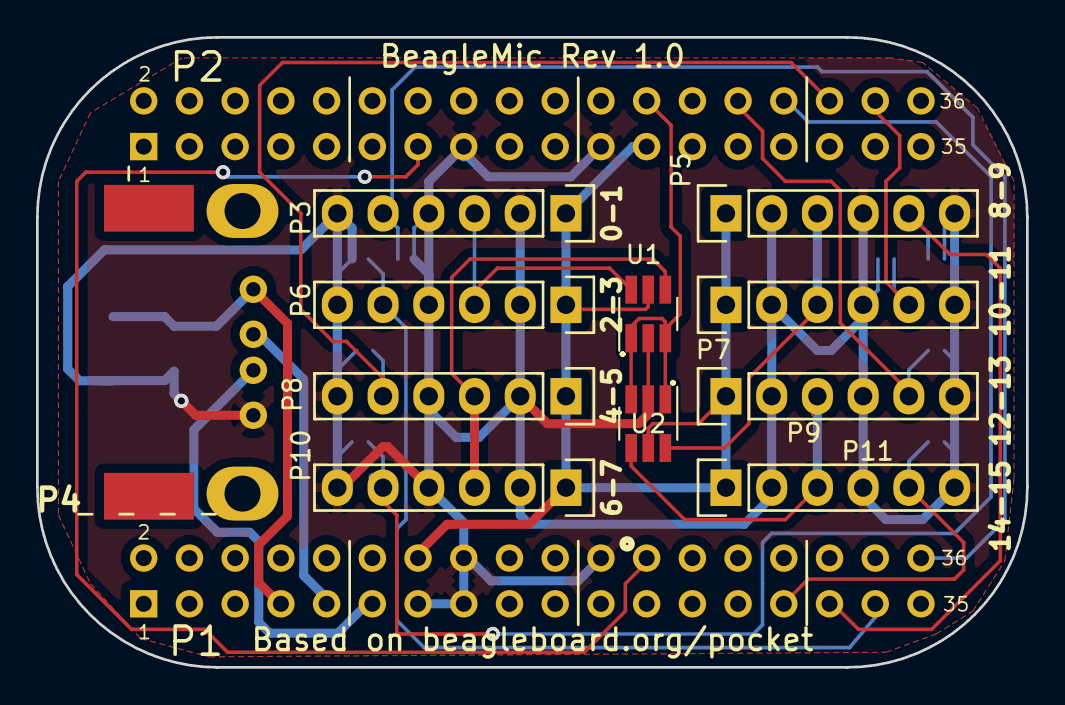
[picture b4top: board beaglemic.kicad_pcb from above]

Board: 2 copper layers, 55.0 x 35.0 mm, 23 parts (0 on the bottom side), 19 nets.

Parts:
C1: 100n; C_0805_HandSoldering
C2: 1u; SMD-1210_Pol
P1, P2: TH-2X18-(35MIL-DIA)-W_O-SILK
P3, P5, P6, P7, P8, P9, P10, P11: CONN_01X06; Pin_Header_Straight_1x06
P4: USB_A; USB-3.5mm(TERES)
R1, R2, R3, R4, R5, R6, R7, R8: 10k; R_0402
U1, U2: 74AUC2G34; SOT-23-6_Handsoldering

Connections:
/(U1.A1)PWM0A: P1.36, P3.5, R1.2
/(U1.A2)PRU-0.1: P1.33, P6.5, R3.2
/(U1.A3)PRU-0.4: P1.31, P5.5, R2.2
/(U1.B1)PRU-0.3: P2.30, P10.5, R7.2
/(U1.B2)PRU-0.2: P2.32, P8.5, R5.2
/(U1.B3)PRU-0.5: P2.34, P7.5, R4.2
/(U1.C3)PRU-0.6: P2.28, P9.5, R6.2
/(U1.C4)PRU-0.7: P1.29, P11.5, R8.2
/(U1.L15)USB1.D+: P1.11, P4.3
/(U1.L16)USB1.D-: P1.9, P4.2
/(U1.P6): P2.24, U1.1, U1.3, U2.1, U2.3
/MIC_CLK_0_3: P3.3, P6.3, U1.6
/MIC_CLK_4_7: P8.3, P10.3, U1.4
/MIC_CLK_8_11: P5.3, P7.3, U2.6
/MIC_CLK_12_15: P9.3, P11.3, U2.4
GND: C1.2, C2.2, P1.13, P1.15, P1.16, P1.22, P2.15, P2.21, P3.2, P3.4, P3.6, P4.4, P5.2, P5.4, P5.6, P6.2, P6.4, P6.6, P7.2, P7.4, P7.6, P8.2, P8.4, P8.6, P9.2, P9.4, P9.6, P10.2, P10.4, P10.6, P11.2, P11.4, P11.6, R1.1, R2.1, R3.1, R4.1, R5.1, R6.1, R7.1, R8.1, U1.2, U2.2
SYS_5V: P1.24, P2.13
USB_DC: C1.1, C2.1, P1.7, P4.1
VDD_3V3B: P1.14, P2.23, P3.1, P5.1, P6.1, P7.1, P8.1, P9.1, P10.1, P11.1, U1.5, U2.5

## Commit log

2014-11-23 Special simulator linker script is now part of the PRU toolchain
2014-12-23 Rewrite firmware for one of the blinking led cores in assembler
    One core in C, and one in assembler.
2014-12-30 Fix the MD5 example
    After the fix for https://github.com/dinuxbg/gnupru/issues/3 we
    need to prefix all symbols with an underscore.
2015-01-03 Fix typo in assembler blinking ledo demo
    We want a blinking led, not a PWM. Also, tweak the rate.
2015-01-03 Add C++ simulator example
2015-02-05 Add C++ blinking led example
2015-02-07 Migrate to the new <pru/io.h> newlib header
2015-03-01 Migrate to the new -mmcu GCC option
2015-03-26 Fix firmware loader handling of BSS
    See https://github.com/dinuxbg/gnupru/issues/7
2015-03-28 Add ov7670 example
2015-03-28 Update README section for blinking-led
2015-03-29 pru-ov7670-cape: Fix erroneous PCLK/VSYNC pin connection
    The two OV7670 pins were inadvertently swapped.
2015-03-29 Fix incorrect comment
2015-04-30 pru-ov7670-cape: Add V1 gerbers and PDF schematics
    Now that the PCB has been verified, publish the production files.
2015-07-11 ov7670-cam:cape: Add errata note about camera connector dimensions
2015-07-11 Reorganize documentation
    Root-directory now contains only the overviews. Sub-directories
    have their own README.md files with detailed instructions.
2015-07-11 ov7670-cam: Add second camera support
    PRU0 now reads data from a second camera, instead of sitting idle.
2015-09-25 Fix per latest <pru/io.h> macors
2015-10-13 Add resource table to blinking-led example
    Firmware now can be loaded and executed by remoteproc.
2015-10-13 Migrate to the new __delay_cycles builtin
2015-10-13 Update blinking-led/pru/Makefile
    Compiling everything at once suits better our small embedded project.
2015-10-13 Move UIO host loader
    No functional changes. Only preparations for the remoteproc example
2015-10-16 Add remoteproc blinking led example
    The kernel driver source is prepatched with a fix for loading PRU Binutils
    ELF images.
2015-10-30 blinking-led:remoteproc: Simplify demo instructions
    Latest RCN's debian image already contains the remoteproc fix
    for Binutils, so module compilation is not needed.
2015-11-28 Add HC-SR04 ultrasound range sensor example
2015-12-31 Utilize the new hi_rlz LDI modifier
2015-12-31 hc-sr05-range-sensor: Cleanup code style
2016-07-19 hc-sr05-range-sensor: Switch from MB to INT for virtio transport
    Latest TI virtqueue driver uses interrupts instead of mailboxes
    for signalling. Update the firmware accordingly.
    Get the rpmsg library from TI pru-software-support-package
    commit 0797ba40928b57c91cbc6e4704b1df0fbb80c9c0.
2016-08-31 Fixes an rpmsg bug concerning available buffers
    The vring implementation used by rpmsg contains a free
    running index for the last available buffer that was
    filled by the ARM side. The PRU rpmsg library also keeps
    track locally of the last available buffer index that it
    consumed in the form of a free running index.
    The PRU rpmsg library can compare the last available index
2016-11-27 Update host notes for latest BB Debian images
2017-01-01 Use LDI32 and remove leading symbol underscores
    This patch updates the source to be compatible with the new
    Binutils/GCC release 2016.12-beta-rc2.
    Now LDI32 is natively supported by the assembler, instead of the old
    %hi/%lo ops.
    GCC has also been updated to output ELF symbols without a leading
    underscore in order to be compatible with TI's ABI.
2018-10-27 Add Makefile rules for binary images
    These rules could be useful if firmware loader does not understand ELF format.
    Example usage:
    make out/pru-core1.dmem.bin
    make out/pru-core1.imem.bin
2018-11-25 Add BeagleMic project
2018-12-15 Add tdmsim project
2018-12-16 Fix pinconfig for BeagleBone White
2019-03-19 Add beaglemic cape errata
2019-04-29 beaglemic: Add stream-stop command
    System should no longer be swamped with RPMSG errors when recording stops.
2019-09-09 Add remoteproc headers to blinking LED examples
    With so much churn in the host driver, let's keep the remoteproc and rpmsg
    headers in the examples. Someday, when remoteproc gets mainlined, we
    could think about a system-wide library (perhaps part of gnuprumcu?).
2019-09-22 beaglemic: Update documentation
    Cape and PDM breakout boards have been validated, and errata has been written.
    So update README to remove the "untested" reference.
2019-09-23 Migrate beaglemic to ALSA
2019-09-23 beaglemic: Update README to account for ALSA migration
2020-01-04 beaglemic: Add documentation for running on BBAI
2020-01-04 beaglemic: INMP621 breakout - rc1
    Initial release for the INMP621 PDM microphone breakout board.
    WARNING - I have not validated it yet!
2020-01-04 beaglemic: BeagleMic Cape - rc1
    Cape allowing to connect 16 PDM breakout boards to either:
    * PocketBeagle
    * BeagleBone AI
    * iCE40HX8K-EVB
    WARNING - I have not validated it yet!
2020-01-04 beaglemic: Additional documentation
2020-01-04 beaglemic: Validate LED strip on PocketBeagle
2020-01-06 Move BeagleMic to external repository
2020-06-25 Added example to demostrate button and LED interaction
2020-06-26 Renamed folder aand removed UiO and other changes
2020-06-26 remove blinking-Butled
2020-06-26 Removed .gdbinit
2020-06-26 Fixed makefile and readme
2020-06-26 Added Fritzing Wiring Diagram
2020-06-26 Changed file to local
2020-06-27 Readjusted relative path
2020-06-27 Edited to remove unneccessay flags
2020-06-27 blinking-led: Cleanup README
2020-06-27 blinking-led: Minor comment fix
2020-06-27 Update instructions for remoteproc enablement
    This fixes github issue #7
2020-06-27 Add button-blinking-led to list of examples
2020-07-13 Added Patch to run hc-sr04-range-sensor code on PRU0
2020-07-13 Added instructions to apply and undo patch
2020-09-03 Updated Readme to use new features of makefile
2020-09-03 - Added logic to makefile that eases loading of firmware and stoping and starting of PRU cores - These new targets will be specially helpful during development when one needs to make new changes to f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
2020-12-04 PRU GNU toolchain is now in mainline
    So remove the "unofficial" marker.
2020-12-27 blinking led: Blink LED using GPIO1_24 USR3 LED on PocketBeagle
2021-07-22 tdmsim: Remove stale project
2021-11-23 kernel-5.10: Port latest changes from mainline
2021-11-24 Update instructions
2021-12-04 Remove empty resource tables
    Mainline kernel can load firmware images without resource table.
2021-12-04 Switch to __R30/__R31 convenient access
    Now that GCC12 supports the more convenient access to __R30 and __R31
    registers, let's use it.
2021-12-24 Warn that remoteproc from kernel 5.10 is now required
2022-01-02 hc-sr04-range-sensor: Fix comment typo
2022-03-19 Re-enable array warning
    Issue has been fixed in GCC mainline: https://gcc.gnu.org/bugzilla/show_bug.cgi?id=99578
2022-09-08 hc-sr04-range-sensor: Remove TI's I/O headers
    This bumps the gnuprumcu requirement to version 0.9.0 or later.
2022-09-10 hc-sr04-range-sensor: Add support for Beaglebone-AI64
2023-05-21 hc-sr04: Port to BeaglePlay
2023-10-24 Add top-level Makefile for internal tests
2023-10-24 remoteproc: Remove stale kernel patch
    The remoteproc driver patch has been in mainline for quite a while now.
2023-10-25 CI: Fix typo
2023-10-25 CI: Fix commands
2023-12-27 DO NOT MERGE - test carry behaviour on real hardware
    Steps:
    cp out/hc-sr04-range-sensor.elf /lib/firmware/
    echo hc-sr04-range-sensor.elf > /sys/class/remoteproc/remoteproc1/firmware
    echo start > /sys/class/remoteproc/remoteproc1/state
    sleep 0.3
    [ -c /dev/rpmsg_pru31 ] || exit 1
2024-01-09 Update for kernel v6.1
    This is a cherry-pick of:
    https://git.ti.com/cgit/pru-software-support-package/pru-software-support-package/commit/?id=52f25a06e7e1c71d0e84ddc25f9c730776f31c44
2024-01-14 Add minimal rust example
    Still highly experimental. So don't mention it in the main README.
2024-05-22 Do not return from main
    The minimal runtime does not support returning from the main() function.
2024-05-28 md5-check: Use string functions from libc
    Compile checked only.
2025-06-01 hc-sr04: Update to kernel v6.12
2025-11-23 rust: Add I/O operations
    gccrs is still highly experimental, but it can now do I/O!
    Tested with the non-released r16-5244-g5a2319b71e4d30 GCC version.
2025-11-23 rust: Add I/O delays
2026-05-01 Cleanup
2026-05-01 Add option to set TI SoC variant to build for
